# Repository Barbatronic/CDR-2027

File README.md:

# Karibous-2027-Differential-Robot

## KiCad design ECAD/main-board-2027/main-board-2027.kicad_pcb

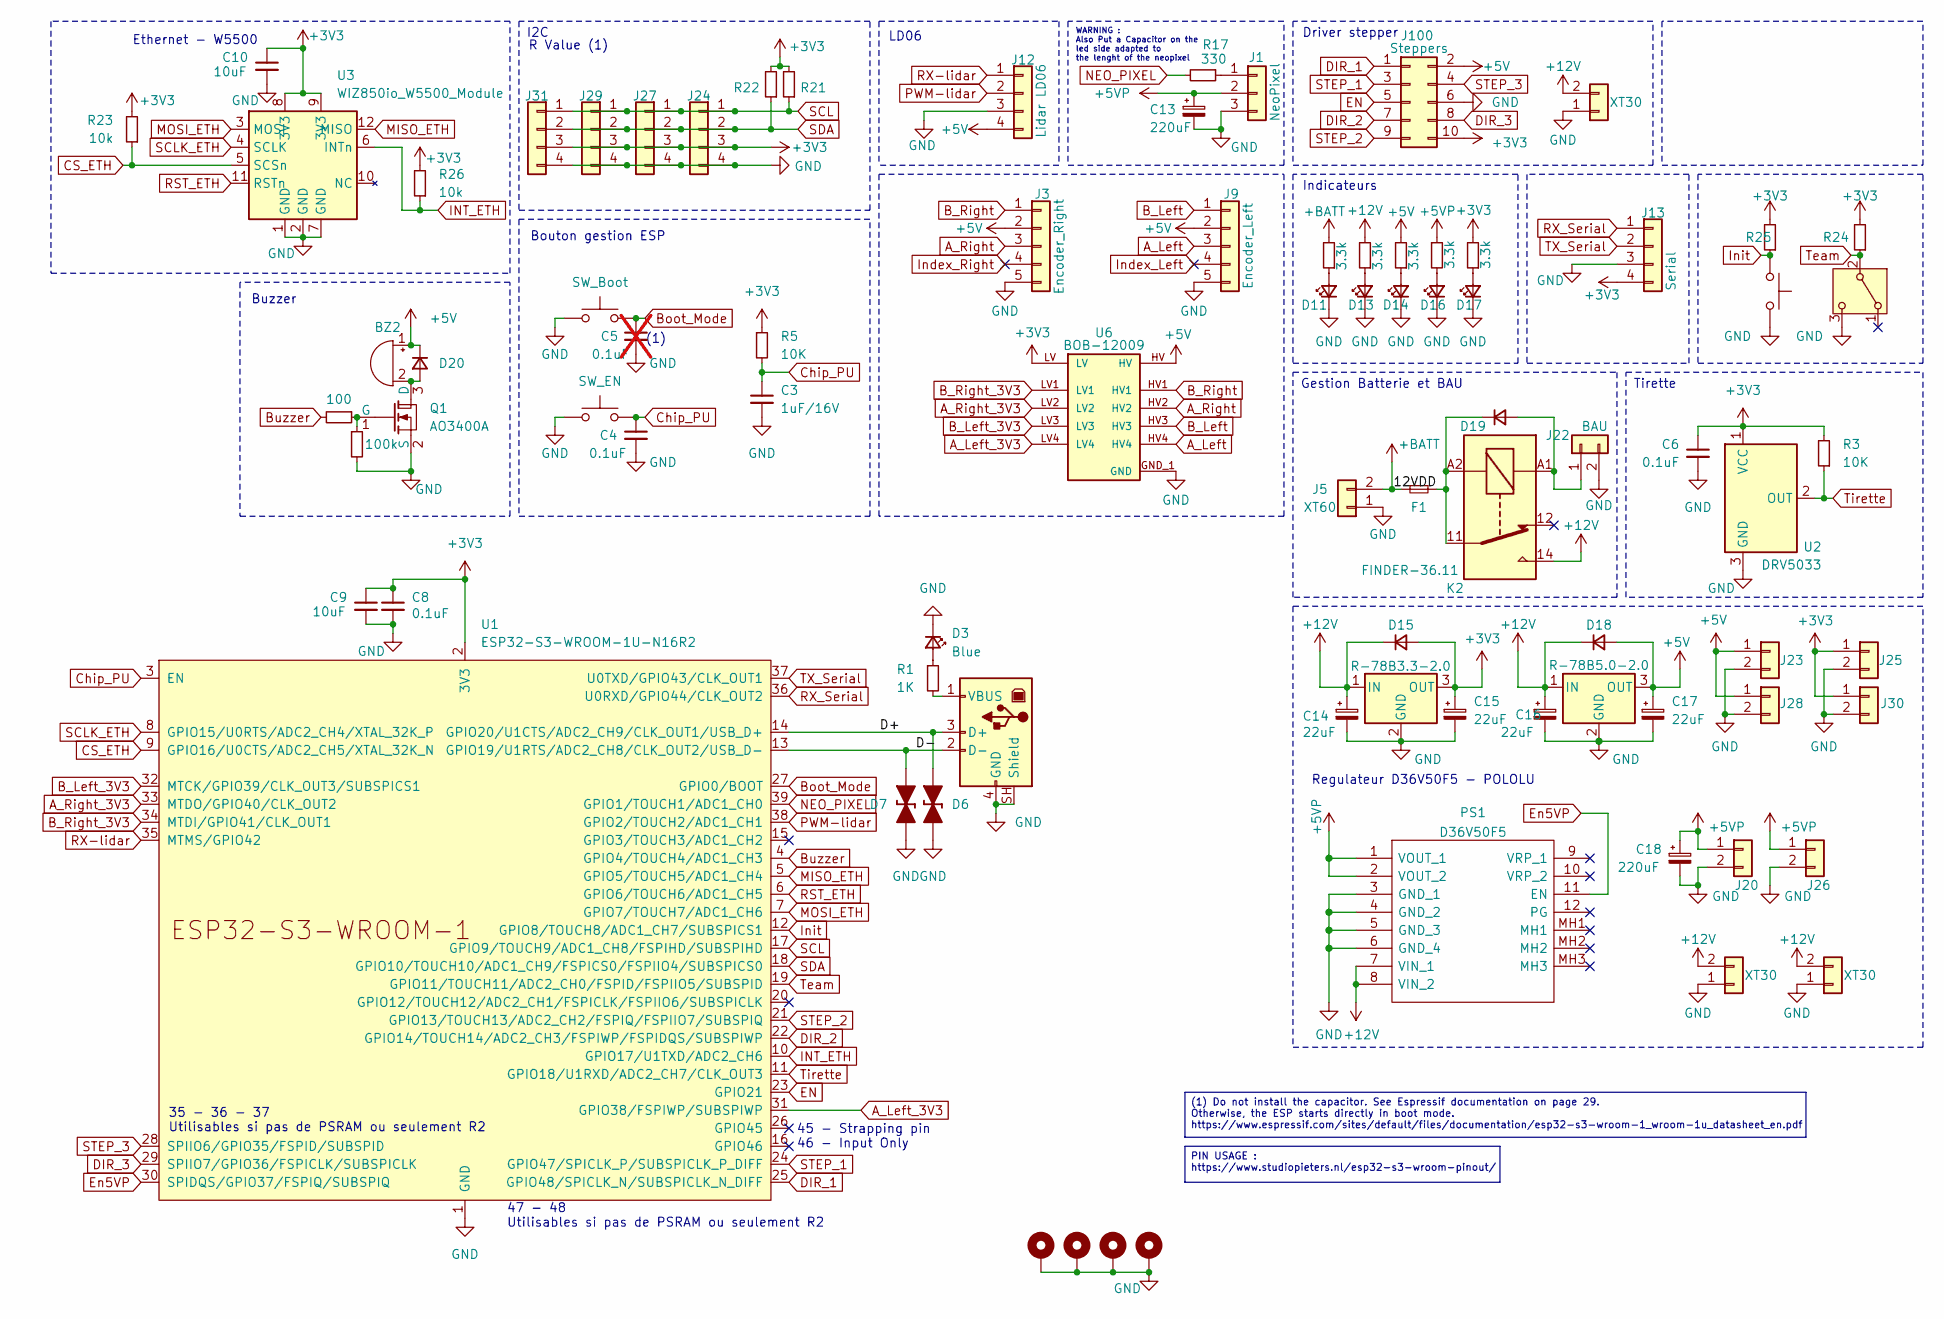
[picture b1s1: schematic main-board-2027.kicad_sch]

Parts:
BZ2: Buzzer; Buzzer_12x9.5RM7.6
C3: 1uF/16V; C_1206_3216Metric
C4: 0.1uF; C_1206_3216Metric
C5: 0.1uF; C_1206_3216Metric; not fitted
C6, C8: 0.1uF; C_1206_3216Metric_Pad1.33x1.80mm_HandSolder
C9, C10: 10uF; C_1206_3216Metric_Pad1.33x1.80mm_HandSolder
C13, C18: 220uF; CP_Radial_D8.0mm_P3.80mm
C14, C15, C16, C17: 22uF; CP_Elec_5x5.4
D3: Blue; LED_1206_3216Metric
D6, D7: D_TVS_Bidirectional_Generic; D_SOD-523
D11, D13, D14, D16, D17: LED_Small; LED_1206_3216Metric_Pad1.42x1.75mm_HandSolder
D15, D18, D19: D_Small; D_SMA_Handsoldering
D20: SS34; D_SMA_Handsoldering
F1: Fuse_Small; Fuseholder_Blade_Mini_Keystone_3568
H5, H6, H7, H8: MountingHole_Pad; MountingHole_3.2mm_M3_Pad_Via
J1: NeoPixel; Molex_KK-254_AE-6410-03A_1x03_P2.54mm_Vertical
J2: USB_B; USB_B_TE_5787834_Vertical
J3: Encoder_Right; Molex_KK-254_AE-6410-05A_1x05_P2.54mm_Vertical
J5: XT60; AMASS_XT60-M_1x02_P7.20mm_Vertical
J9: Encoder_Left; Molex_KK-254_AE-6410-05A_1x05_P2.54mm_Vertical
J12: Lidar LD06; Molex_KK-254_AE-6410-04A_1x04_P2.54mm_Vertical
J13: Serial; Molex_KK-254_AE-6410-04A_1x04_P2.54mm_Vertical
J16, J17, J18: XT30; AMASS_XT30U-F_1x02_P5.0mm_Vertical
J20, J26: Molex_KK-396_A-41791-0002_1x02_P3.96mm_Vertical
J22: BAU; Molex_KK-396_A-41791-0002_1x02_P3.96mm_Vertical
J23, J25, J28, J30: Conn_01x02; Molex_KK-254_AE-6410-02A_1x02_P2.54mm_Vertical
J24, J27, J29, J31: External tools; Molex_KK-254_AE-6410-04A_1x04_P2.54mm_Vertical
J100: Steppers; IDC-Header_2x05_P2.54mm_Vertical
K2: FINDER-36.11; Relay_SPDT_Finder_36.11
PS1: D36V50F5; Manufacturer_Part_Number D36V50F5
Q1: AO3400A; SOT-23_Handsoldering
R1: 1K; R_1206_3216Metric_Pad1.30x1.75mm_HandSolder
R3, R5: 10K; R_1206_3216Metric_Pad1.30x1.75mm_HandSolder
R15, R16, R18, R19, R20: 3.3k; R_1206_3216Metric_Pad1.30x1.75mm_HandSolder
R17: 330; R_1206_3216Metric_Pad1.30x1.75mm_HandSolder
R21, R22: 4.7k; R_1206_3216Metric_Pad1.30x1.75mm_HandSolder
R23, R24, R25, R26: 10k; R_1206_3216Metric_Pad1.30x1.75mm_HandSolder
R27: 100; R_1206_3216Metric_Pad1.30x1.75mm_HandSolder
R28: 100k; R_1206_3216Metric_Pad1.30x1.75mm_HandSolder
SW1: SW_SPDT; SK-12D10 1P2T
SW2: SW_Push; SW_Cherry_MX_PCB
SWBoot1: SW_Boot; SW_SPST_CK_RS282G05A3
SWEn1: SW_EN; SW_SPST_CK_RS282G05A3
U1: ESP32-S3-WROOM-1U-N16R2; ESP32-S3-WROOM-1U
U2: DRV5033; SOT-23_Handsoldering
U3: WIZ850io_W5500_Module
U6: BOB-12009; CONV_BOB-12009; PARTREV 01
U7: R-78B3.3-2.0; Converter_DCDC_RECOM_R-78B-2.0_THT
U8: R-78B5.0-2.0; Converter_DCDC_RECOM_R-78B-2.0_THT

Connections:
+3V3: C6.1, C8.1, C9.1, C10.1, C15.1, D15.2 (A), J13.4, J24.3, J25.1, J27.3, J29.3, J30.1, J31.3, J100.10, R3.2, R5.1, R20.2, R21.2, R22.2, R23.2, R24.2, R25.2, R26.2, U1.2 (3V3), U2.1 (VCC), U3.8 (3V3), U3.9 (3V3), U6.LV, U7.3 (OUT)
+5V: BZ2.1 (+), C17.1, D18.2 (A), D20.1 (K), J3.2, J9.2, J12.4, J23.1, J28.1, J100.2, R18.2, U6.HV, U8.3 (OUT)
+5VP: C13.1, C18.1, J1.2, J20.1, J26.1, PS1.1 (VOUT_1), PS1.2 (VOUT_2), R19.1
+12V: C14.1, C16.1, D15.1 (K), D18.1 (K), J16.2, J17.2, J18.2, K2.14, PS1.7 (VIN_1), PS1.8 (VIN_2), R16.2, U7.1 (IN), U8.1 (IN)
+BATT: F1.1, J5.2, R15.2
/12VDD: D19.1 (K), F1.2, K2.11, K2.A2
/D+: D6.2 (A), J2.3 (D+), U1.14 (GPIO20/U1CTS/ADC2_CH9/CLK_OUT1/USB_D+)
/D-: D7.2 (A), J2.2 (D-), U1.13 (GPIO19/U1RTS/ADC2_CH8/CLK_OUT2/USB_D-)
A_Left: J9.3, U6.HV4
A_Left_3V3: U1.31 (GPIO38/FSPIWP/SUBSPIWP), U6.LV4
A_Right: J3.3, U6.HV2
A_Right_3V3: U1.33 (MTDO/GPIO40/CLK_OUT2), U6.LV2
B_Left: J9.1, U6.HV3
B_Left_3V3: U1.32 (MTCK/GPIO39/CLK_OUT3/SUBSPICS1), U6.LV3
B_Right: J3.1, U6.HV1
B_Right_3V3: U1.34 (MTDI/GPIO41/CLK_OUT1), U6.LV1
Boot_Mode: C5.1, SWBoot1.2, U1.27 (GPIO0/BOOT)
Buzzer: R27.2, U1.4 (GPIO4/TOUCH4/ADC1_CH3)
CS_ETH: R23.1, U1.9 (GPIO16/U0CTS/ADC2_CH5/XTAL_32K_N), U3.5 (SCSn)
Chip_PU: C3.1, C4.1, R5.2, SWEn1.2, U1.3 (EN)
DIR_1: J100.1, U1.25 (GPIO48/SPICLK_N/SUBSPICLK_N_DIFF)
DIR_2: J100.7, U1.22 (GPIO14/TOUCH14/ADC2_CH3/FSPIWP/FSPIDQS/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)
DIR_3: J100.8, U1.29 (SPIIO7/GPIO36/FSPICLK/SUBSPICLK)
EN: J100.5, U1.23 (GPIO21)
En5VP: PS1.11 (EN), U1.30 (SPIDQS/GPIO37/FSPIQ/SUBSPIQ)
GND: C3.2, C4.2, C5.2, C6.2, C8.2, C9.2, C10.2, C13.2, C14.2, C15.2, C16.2, C17.2, C18.2, D3.1 (K), D6.1 (K), D7.1 (K), D11.1 (K), D13.1 (K), D14.1 (K), D16.1 (K), D17.1 (K), H5.1 (1_1), H6.1 (1_1), H7.1 (1_1), H8.1 (1_1), J1.3, J2.4 (GND), J2.SH (Shield), J3.5, J5.1, J9.5, J12.3, J13.3, J16.1, J17.1, J18.1, J20.2, J22.2, J23.2, J24.4, J25.2, J26.2, J27.4, J28.2, J29.4, J30.2, J31.4, J100.6, PS1.3 (GND_1), PS1.4 (GND_2), PS1.5 (GND_3), PS1.6 (GND_4), Q1.2 (S), R28.2, SW1.3 (C), SW2.2, SWBoot1.1, SWEn1.1, U1.1 (GND), U1.40 (GND), U1.41 (GND), U2.3 (GND), U3.1 (GND), U3.2 (GND), U3.7 (GND), U6.GND_1 (GND), U6.GND_2 (GND), U7.2 (GND), U8.2 (GND)
INT_ETH: R26.1, U1.10 (GPIO17/U1TXD/ADC2_CH6), U3.6 (INTn)
Index_Left: J9.4
Index_Right: J3.4
Init: R25.1, SW2.1, U1.12 (GPIO8/TOUCH8/ADC1_CH7/SUBSPICS1)
MISO_ETH: U1.5 (GPIO5/TOUCH5/ADC1_CH4), U3.12 (MISO)
MOSI_ETH: U1.7 (GPIO7/TOUCH7/ADC1_CH6), U3.3 (MOSI)
NEO_PIXEL: R17.2, U1.39 (GPIO1/TOUCH1/ADC1_CH0)
unnamed: BZ2.2 (-), D20.2 (A), Q1.3 (D)
unnamed: D3.2 (A), R1.1
unnamed: D11.2 (A), R15.1
unnamed: D13.2 (A), R16.1
unnamed: D14.2 (A), R18.1
unnamed: D16.2 (A), R19.2
unnamed: D17.2 (A), R20.1
unnamed: D19.2 (A), J22.1, K2.A1
unnamed: J1.1, R17.1
unnamed: J2.1 (VBUS), R1.2
unnamed: Q1.1 (G), R27.1, R28.1
PWM-lidar: J12.2, U1.38 (GPIO2/TOUCH2/ADC1_CH1)
RST_ETH: U1.6 (GPIO6/TOUCH6/ADC1_CH5), U3.11 (RSTn)
RX-lidar: J12.1, U1.35 (MTMS/GPIO42)
RX_Serial: J13.1, U1.36 (U0RXD/GPIO44/CLK_OUT2)
SCL: J24.1, J27.1, J29.1, J31.1, R21.1, U1.17 (GPIO9/TOUCH9/ADC1_CH8/FSPIHD/SUBSPIHD)
SCLK_ETH: U1.8 (GPIO15/U0RTS/ADC2_CH4/XTAL_32K_P), U3.4 (SCLK)
SDA: J24.2, J27.2, J29.2, J31.2, R22.1, U1.18 (GPIO10/TOUCH10/ADC1_CH9/FSPICS0/FSPIIO4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)
STEP_1: J100.3, U1.24 (GPIO47/SPICLK_P/SUBSPICLK_P_DIFF)
STEP_2: J100.9, U1.21 (GPIO13/TOUCH13/ADC2_CH2/FSPIQ/FSPIIO7/S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)
STEP_3: J100.4, U1.28 (SPIIO6/GPIO35/FSPID/SUBSPID)
TX_Serial: J13.2, U1.37 (U0TXD/GPIO43/CLK_OUT1)
Team: R24.1, SW1.2 (B), U1.19 (GPIO11/TOUCH11/ADC2_CH0/FSPID/FSPIIO5/S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)
Tirette: R3.1, U1.11 (GPIO18/U1RXD/ADC2_CH7/CLK_OUT3), U2.2 (OUT)

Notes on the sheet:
WARNING : Also Put a Capacitor on the led side adapted to the lenght of the neopixel
R Value (1)
Buzzer
I2C
Gestion Batterie et BAU
Ethernet - W5500
35 - 36 - 37 Utilisables si pas de PSRAM ou seulement R2
Bouton gestion ESP
Tirette
(1)
LD06
47 - 48 Utilisables si pas de PSRAM ou seulement R2
Indicateurs
45 - Strapping pin 46 - Input Only
Regulateur D36V50F5 - POLOLU
Driver stepper
PIN USAGE : https://www.studiopieters.nl/esp32-s3-wroom-pinout/
(1) Do not install the capacitor. See Espressif documentation on page 29. Otherwise, the ESP starts directly in boot mode. https://www.espressif.com/sites/default/files/documentation/esp32-s3-wroom-1_wroom-1u_datasheet_en.pdf

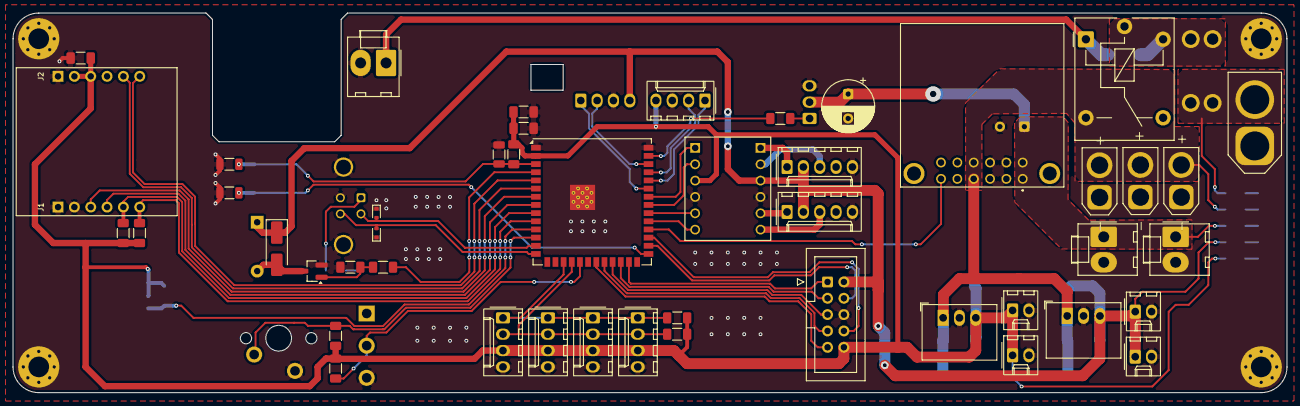
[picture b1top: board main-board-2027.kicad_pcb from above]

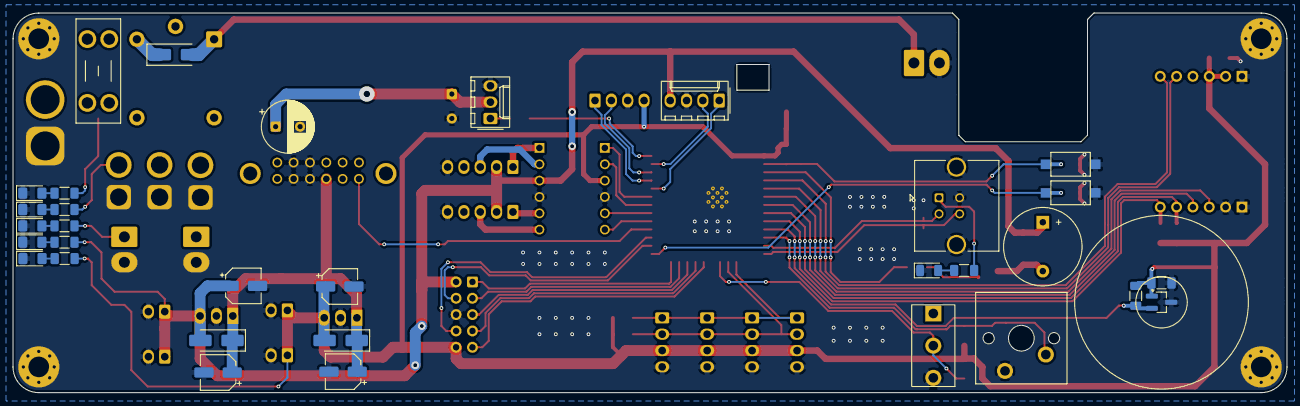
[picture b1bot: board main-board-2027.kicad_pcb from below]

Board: 2 copper layers, 198.0 x 59.0 mm, 83 parts (32 on the bottom side), 55 nets.

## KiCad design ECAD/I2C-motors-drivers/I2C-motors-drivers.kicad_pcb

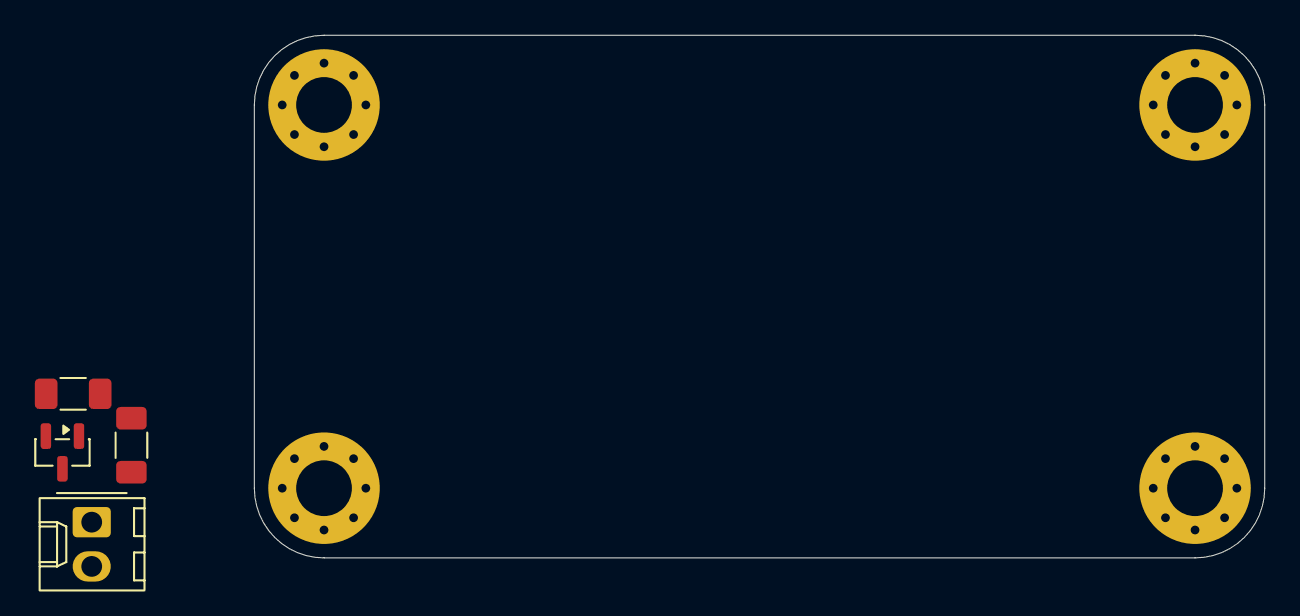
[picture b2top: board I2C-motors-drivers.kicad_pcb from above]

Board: 2 copper layers, 58.0 x 30.0 mm, 9 parts (1 on the bottom side), 4 nets, no tracks yet.

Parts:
D4: D_Small; D_SMA_Handsoldering
H1, H2, H3, H4: MountingHole_Pad_MP; MountingHole_3.2mm_M3_Pad_Via
J3: CON_EV; Molex_KK-254_AE-6410-02A_1x02_P2.54mm_Vertical
Q1: AO3400A; SOT-23
R5: 270R; R_1206_3216Metric_Pad1.30x1.75mm_HandSolder
R7: 10K; R_1206_3216Metric_Pad1.30x1.75mm_HandSolder

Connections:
12V: D4.1 (K), J3.2
GND: Q1.2 (S), R7.2
unnamed: D4.2 (A), J3.1, Q1.3 (D)
unnamed: Q1.1 (G), R5.1, R7.1

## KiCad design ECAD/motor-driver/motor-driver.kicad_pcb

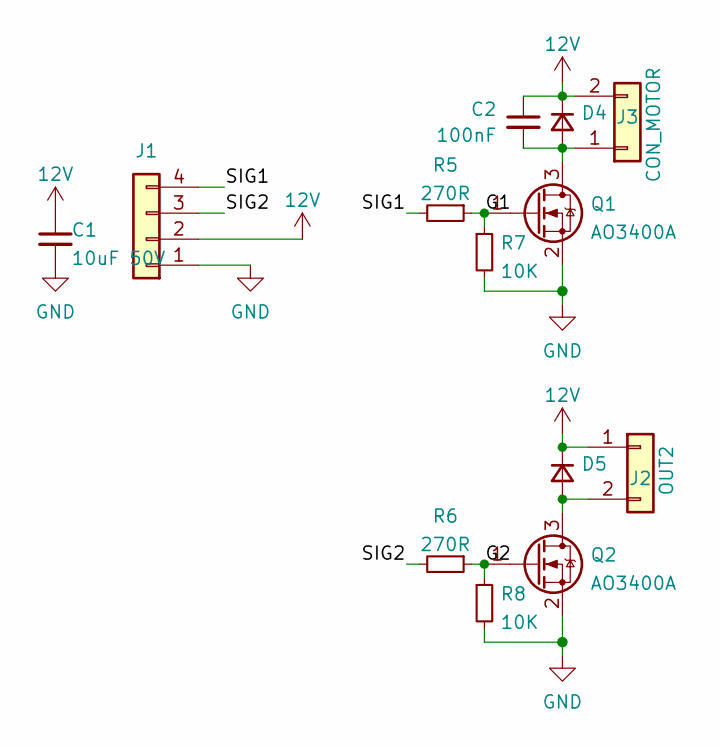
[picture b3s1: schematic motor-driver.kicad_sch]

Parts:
C1: 10uF 50V; C_1206_3216Metric; LCSC C13585
C2: 100nF; C_1206_3216Metric; LCSC C24497
D4, D5: SS34; D_SMA; LCSC C8678
J1: Conn_01x04; Molex_KK-254_AE-6410-04A_1x04_P2.54mm_Vertical
J2: OUT2; Molex_KK-254_AE-6410-02A_1x02_P2.54mm_Vertical
J3: CON_MOTOR; Moteur_Cosses_2xFente_3.6x2.2mm_R10.6mm
Q1, Q2: AO3400A; SOT-23; LCSC C20917
R5, R6: 270R; R_1206_3216Metric; LCSC C4466
R7, R8: 10K; R_1206_3216Metric; LCSC C17902

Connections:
12V: C1.1, C2.1, D4.1 (K), D5.1 (K), J1.2, J2.1, J3.2
/G1: Q1.1 (G), R5.1, R7.1
/G2: Q2.1 (G), R6.1, R8.1
/SIG1: J1.4, R5.2
/SIG2: J1.3, R6.2
GND: C1.2, J1.1, Q1.2 (S), Q2.2 (S), R7.2, R8.2
unnamed: C2.2, D4.2 (A), J3.1, Q1.3 (D)
unnamed: D5.2 (A), J2.2, Q2.3 (D)

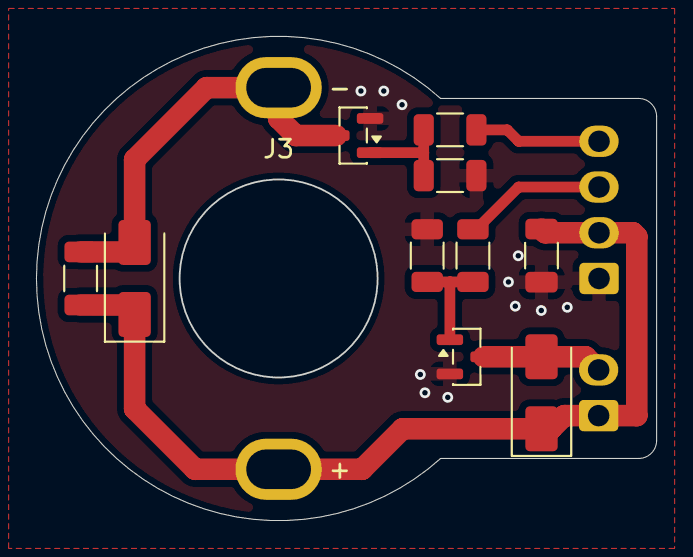
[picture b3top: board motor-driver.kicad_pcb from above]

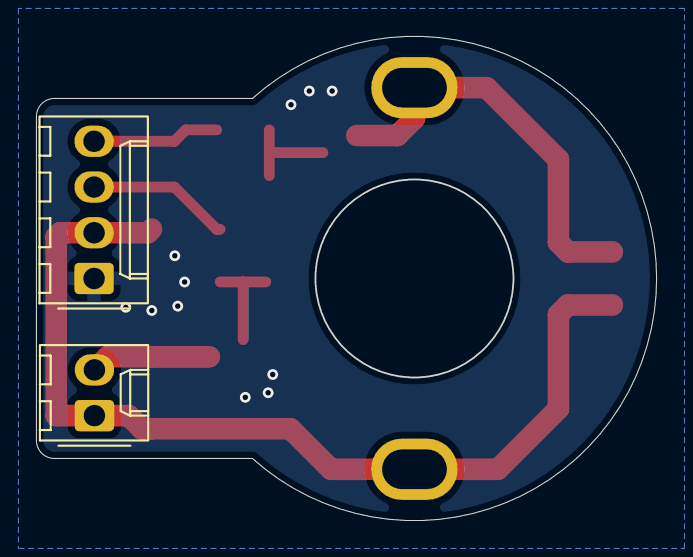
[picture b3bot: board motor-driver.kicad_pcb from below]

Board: 2 copper layers, 34.5 x 26.9 mm, 13 parts (2 on the bottom side), 8 nets.
